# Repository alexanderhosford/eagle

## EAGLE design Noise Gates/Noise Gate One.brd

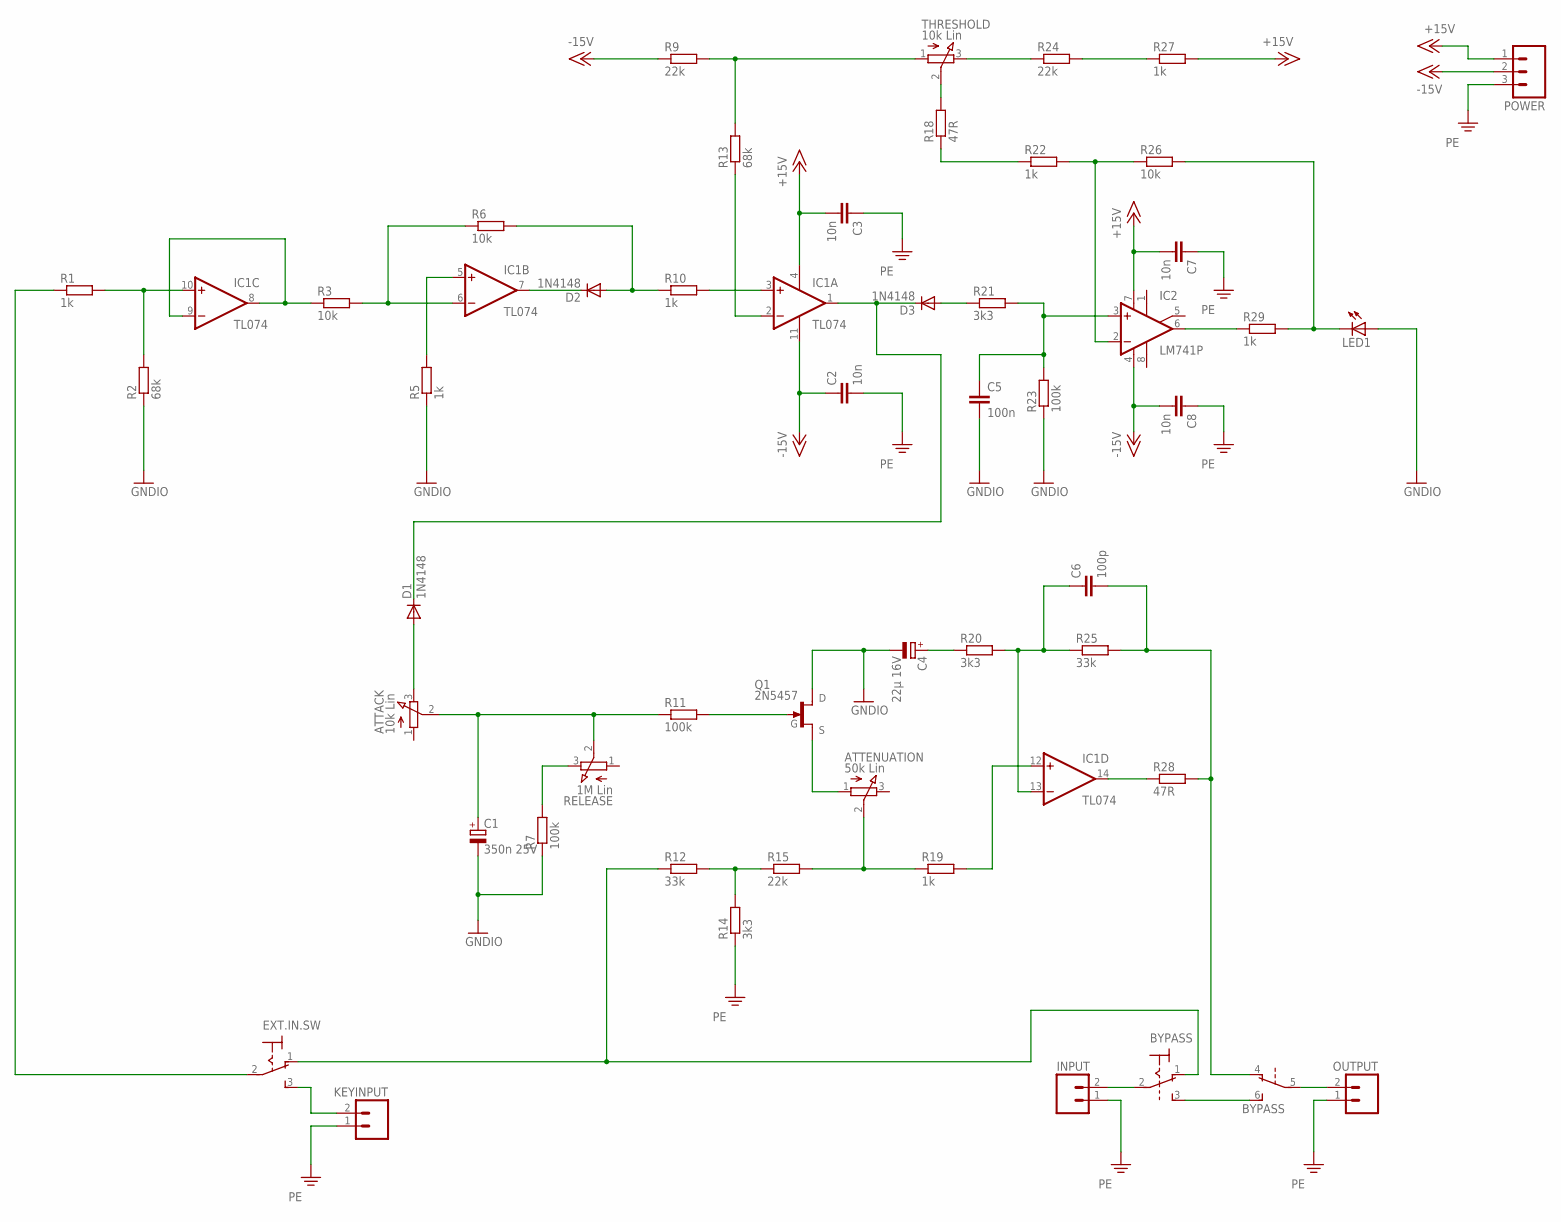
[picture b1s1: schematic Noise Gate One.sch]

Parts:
ATTACK: 10k Lin; 3RP/1610N
ATTENUATION: 50k Lin; 3RP/1610N
BYPASS: M9040P2
C1: 350n 25V; E2,5-7
C2, C3, C7, C8: 10n; C050-035X075
C4: 22µ 16V; E2,5-7
C5: 100n; C050-035X075
C6: 100p; C050-035X075
D1, D2, D3: 1N4148; DO35-7
EXT.IN.SW: M9040P
IC1: TL074; DIL14
IC2: LM741P; DIL08
INPUT: M023.5MM; SCREWTERMINAL-3.5MM-2
KEYINPUT: M023.5MM; SCREWTERMINAL-3.5MM-2
LED1: LED5MM
OUTPUT: M023.5MM; SCREWTERMINAL-3.5MM-2
POWER: M03SCREW; SCREWTERMINAL-3.5MM-3
Q1: 2N5457; TO92-
R1, R5, R10, R19, R22, R27, R29: 1k; 0207/7
R2, R13: 68k; 0207/7
R3, R6, R26: 10k; 0207/7
R7, R11, R23: 100k; 0207/7
R9, R15, R24: 22k; 0207/7
R12, R25: 33k; 0207/7
R14, R20, R21: 3k3; 0207/7
R18, R28: 47R; 0207/7
RELEASE: 1M Lin; 3RP/1610N
THRESHOLD: 10k Lin; 3RP/1610N

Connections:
+15V: C3.2, C7.2, IC1.4 (V+), IC2.7 (V+), POWER.1, R27.2
-15V: C2.1, C8.2, IC1.11 (V-), IC2.4 (V-), POWER.2, R9.1
EXT.IN: EXT.IN.SW.3 (S), KEYINPUT.2
GND: C1.-, C4.-, C5.2, LED1.A, Q1.1 (D), R2.1, R5.1, R7.1, R23.1
unnamed: IC2.6 (OUT), R29.1
unnamed: D2.A, R6.2, R10.1
unnamed: C5.1, IC2.3 (+IN), R21.2, R23.2
unnamed: D3.A, R21.1
unnamed: R9.2, R13.2, THRESHOLD.1 (A)
unnamed: LED1.K (C), R26.2, R29.2
unnamed: D1.C, D3.C, IC1.1 (OUT)
unnamed: IC2.2 (-IN), R22.2, R26.1
unnamed: IC1.3 (+IN), R10.2
unnamed: IC1.2 (-IN), R13.1
unnamed: R24.1, THRESHOLD.3 (E)
unnamed: R24.2, R27.1
unnamed: R18.2, THRESHOLD.2 (S)
unnamed: R18.1, R22.1
unnamed: D2.C, IC1.7 (OUT)
unnamed: IC1.6 (-IN), R3.2, R6.1
unnamed: IC1.5 (+IN), R5.2
unnamed: Q1.3 (G), R11.2
unnamed: IC1.8 (OUT), IC1.9 (-IN), R3.1
unnamed: IC1.10 (+IN), R1.2, R2.2
unnamed: BYPASS.4 (O), C6.2, R25.2, R28.2
unnamed: C4.+, R20.1
unnamed: ATTENUATION.1 (A), Q1.2 (S)
unnamed: ATTENUATION.2 (S), R15.2, R19.1
unnamed: R12.2, R14.2, R15.1
unnamed: IC1.12 (+IN), R19.2
unnamed: C6.1, IC1.13 (-IN), R20.2, R25.1
unnamed: ATTACK.2 (S), C1.+, R11.1, RELEASE.2 (S)
unnamed: IC1.14 (OUT), R28.1
unnamed: R7.2, RELEASE.3 (E)
unnamed: ATTACK.3 (E), D1.A
unnamed: EXT.IN.SW.2, R1.1
unnamed: BYPASS.1 (O), EXT.IN.SW.1 (O), R12.1
unnamed: BYPASS.2, INPUT.2
unnamed: BYPASS.5, OUTPUT.2
unnamed: BYPASS.3 (S), BYPASS.6 (S)
PE: C2.2, C3.1, C7.1, C8.1, INPUT.1, KEYINPUT.1, OUTPUT.1, POWER.3, R14.1

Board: 2 copper layers, 50 parts (0 on the bottom side), 41 nets, no tracks yet.

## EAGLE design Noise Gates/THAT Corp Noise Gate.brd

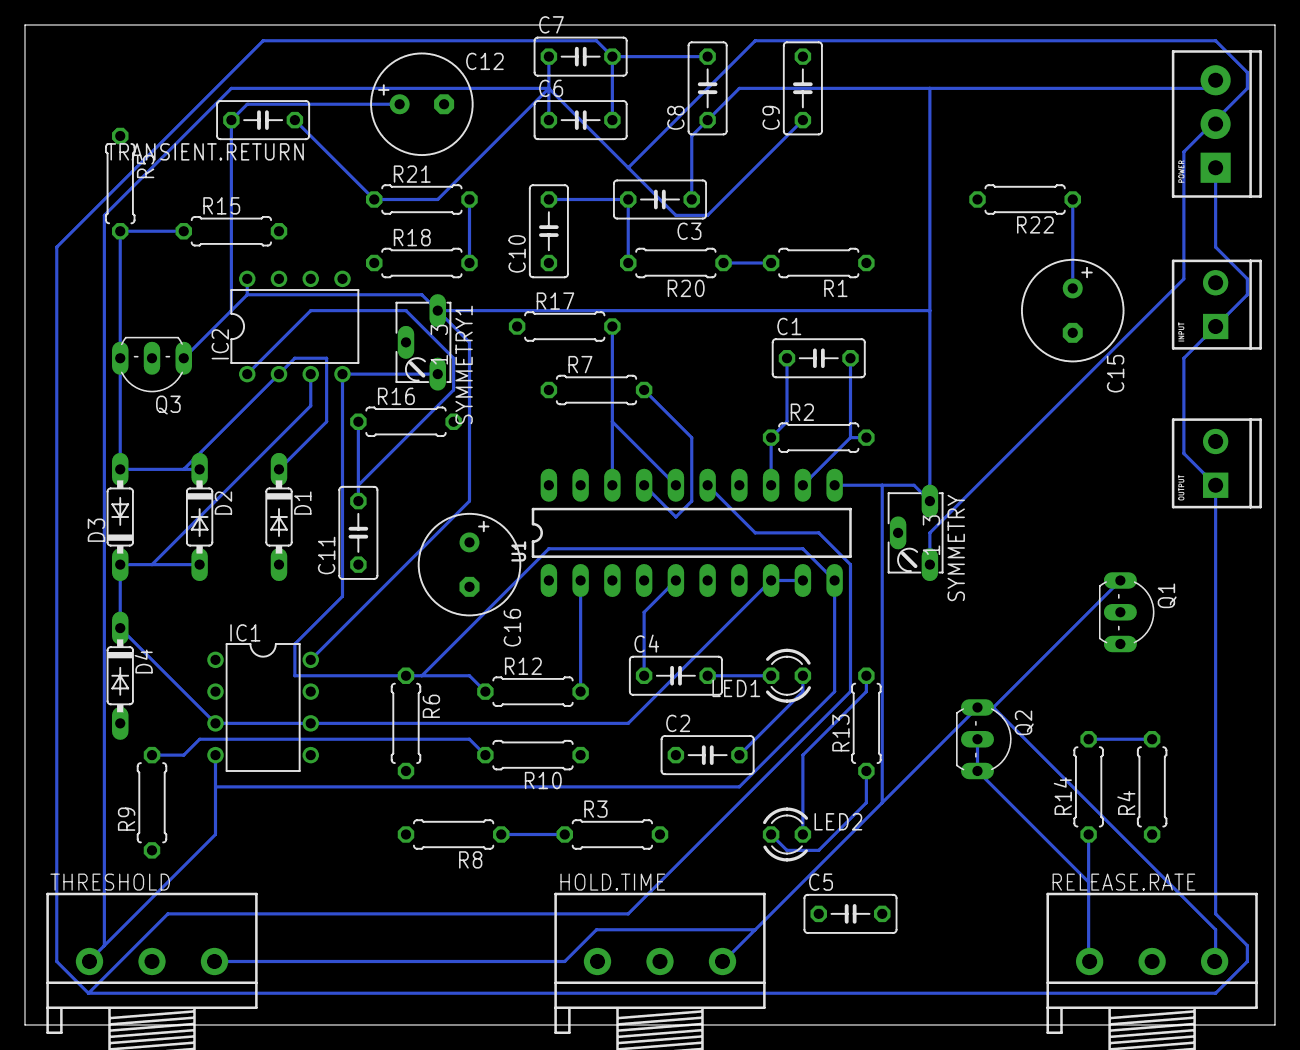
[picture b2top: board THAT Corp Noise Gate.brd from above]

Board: 2 copper layers, 100.0 x 80.0 mm, 55 parts (0 on the bottom side), 34 nets.

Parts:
C1: 47p; C050-030X075
C2, C3, C6, C7, C8, C9, C10: 100n; C050-030X075
C4: 50n; C050-030X075
C5: 2n2; C050-030X075
C11: 220n; C050-030X075
C12: 10µ; E3,5-8
C15, C16: 47µ; E3,5-8
D1, D2, D3, D4: 1N4148; DO35-7
HOLD.TIME: 20k; 3RP/1610N
IC1: LM393N; DIL08
IC2: LF353N; DIL08
INPUT: SCREWTERMINAL-3.5MM-2
LED1, LED2: LED3MM
OUTPUT: SCREWTERMINAL-3.5MM-2
POWER: SCREWTERMINAL-3.5MM-3
Q1, Q2, Q3: 2SA1015; TO92-CBE
R1: 300k; 0207/7
R2, R3, R7: 20k; 0207/7
R4: 30k; 0207/7
R5, R14: 10k; 0207/7
R6, R16: 100k; 0207/7
R8: 5k1; 0207/7
R9: 150k; 0207/7
R10: 2k; 0207/7
R12, R18: 2M; 0207/7
R13: 1M; 0207/7
R15: 1k; 0207/7
R17: 2k49; 0207/7
R20: 51R; 0207/7
R21: 110k; 0207/7
R22: 28k8; 0207/7
RELEASE.RATE: 20k; 3RP/1610N
SYMMETRY, SYMMETRY1: 50k; B64W
THRESHOLD: 50k; 3RP/1610N
TRANSIENT.RETURN: 100n; C050-030X075
U1: THAT4301P20-I; DIL20

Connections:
+15V: C3.1, C8.1, C12.+, HOLD.TIME.3, IC1.8, IC2.8, POWER.3, Q1.E, Q2.E, Q3.E, RELEASE.RATE.3, SYMMETRY.E, SYMMETRY1.E, THRESHOLD.3, TRANSIENT.RETURN.2, U1.11
-15V: C6.1, C7.1, C9.1, IC1.4, IC2.4, POWER.2, R6.1, R12.1, R21.1, SYMMETRY.A, SYMMETRY1.A, THRESHOLD.1, TRANSIENT.RETURN.1, U1.10
GND: D2.A, D3.C, D4.C, IC1.3, IC1.6, IC2.3, U1.8, U1.9
unnamed: R1.2, R20.1, U1.14
unnamed: R1.1, SYMMETRY.S
unnamed: HOLD.TIME.1, Q2.B, Q2.C, R6.2, R8.2, R14.1, RELEASE.RATE.1
unnamed: C1.2, OUTPUT.2, R2.2, U1.12
unnamed: C1.1, R2.1, U1.13
unnamed: HOLD.TIME.2, R3.2
unnamed: R4.1, RELEASE.RATE.2
unnamed: C15.-, R7.1
unnamed: Q3.B, R4.2, R14.2
unnamed: C11.2, IC2.1, R16.1
unnamed: C11.1, D1.A, R15.2
unnamed: R16.2, R17.1
unnamed: C10.1, D4.A, IC1.1, IC1.5, Q1.C
unnamed: IC1.7, R5.1
unnamed: D1.C, D2.C, D3.A, IC2.2, Q3.C, R5.2, R15.1
unnamed: R18.1, SYMMETRY1.S
unnamed: R18.2, R21.2, U1.19
unnamed: R17.2, U1.16, U1.18
unnamed: R9.1, THRESHOLD.2
unnamed: IC1.2, R9.2, R10.2
unnamed: R10.1, U1.4
unnamed: C2.1, C4.1, U1.5
unnamed: C2.2, C5.2, LED1.A, LED2.K, R13.2, U1.7
unnamed: C4.2, C5.1, LED1.K, LED2.A, R13.1, U1.6
unnamed: R12.2, U1.2
unnamed: C16.-, U1.1
unnamed: C16.+, R22.2
unnamed: C15.+, INPUT.2, R22.1
unnamed: Q1.B, R3.1, R8.1
unnamed: R7.2, U1.17
PE: C3.2, C6.2, C7.2, C8.2, C9.2, C10.2, C12.-, INPUT.1, OUTPUT.1, POWER.1, R20.2, U1.15

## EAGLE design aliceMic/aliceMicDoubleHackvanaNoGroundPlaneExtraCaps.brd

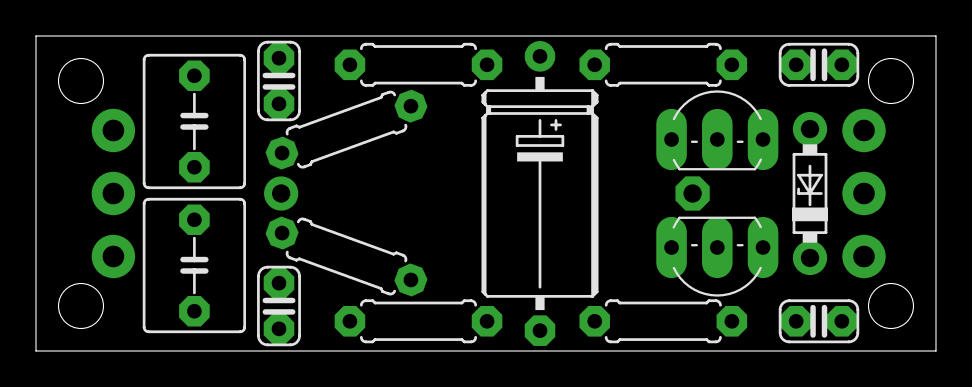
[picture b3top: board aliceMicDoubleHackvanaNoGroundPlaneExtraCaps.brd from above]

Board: 2 copper layers, 50.0 x 17.5 mm, 19 parts (1 on the bottom side), 10 nets, no tracks yet.

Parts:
C1: 100µ; E22-9
C2, C3: µ47; C050-055X075
C4: 10µ; E15-6
C5, C6: 22n; C025-024X044
C7, C8: 470p; C025-024X044
D1: 12V; 7MMGRIDZENER
FET_D_S_1G: 3.5MM_PADS
R1, R2: 2k2; 0207/7
R3: 330R; 0207/7
R4, R5: 100k; 0207/7
R6: 6k8; 0207/7
T1, T2: 2N5087; TO92-EBC
XLR: 3.5MM_PADS

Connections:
GND: C1.-, C4.-, C5.2, C6.1, D1.A, FET_D_S_1G.1, R2.1, XLR.2
unnamed: C4.+, D1.C, R3.2, R6.2
unnamed: C7.2, C8.1, R4.1, R5.2, R6.1, T1.C, T2.C
unnamed: C5.1, T1.E, XLR.3
unnamed: C6.2, T2.E, XLR.1
unnamed: C2.2, C7.1, R4.2, T1.B
unnamed: C3.1, C8.2, R5.1, T2.B
unnamed: C1.+, R1.2, R3.1
unnamed: C2.1, FET_D_S_1G.3, R1.1
unnamed: C3.2, FET_D_S_1G.2, R2.2

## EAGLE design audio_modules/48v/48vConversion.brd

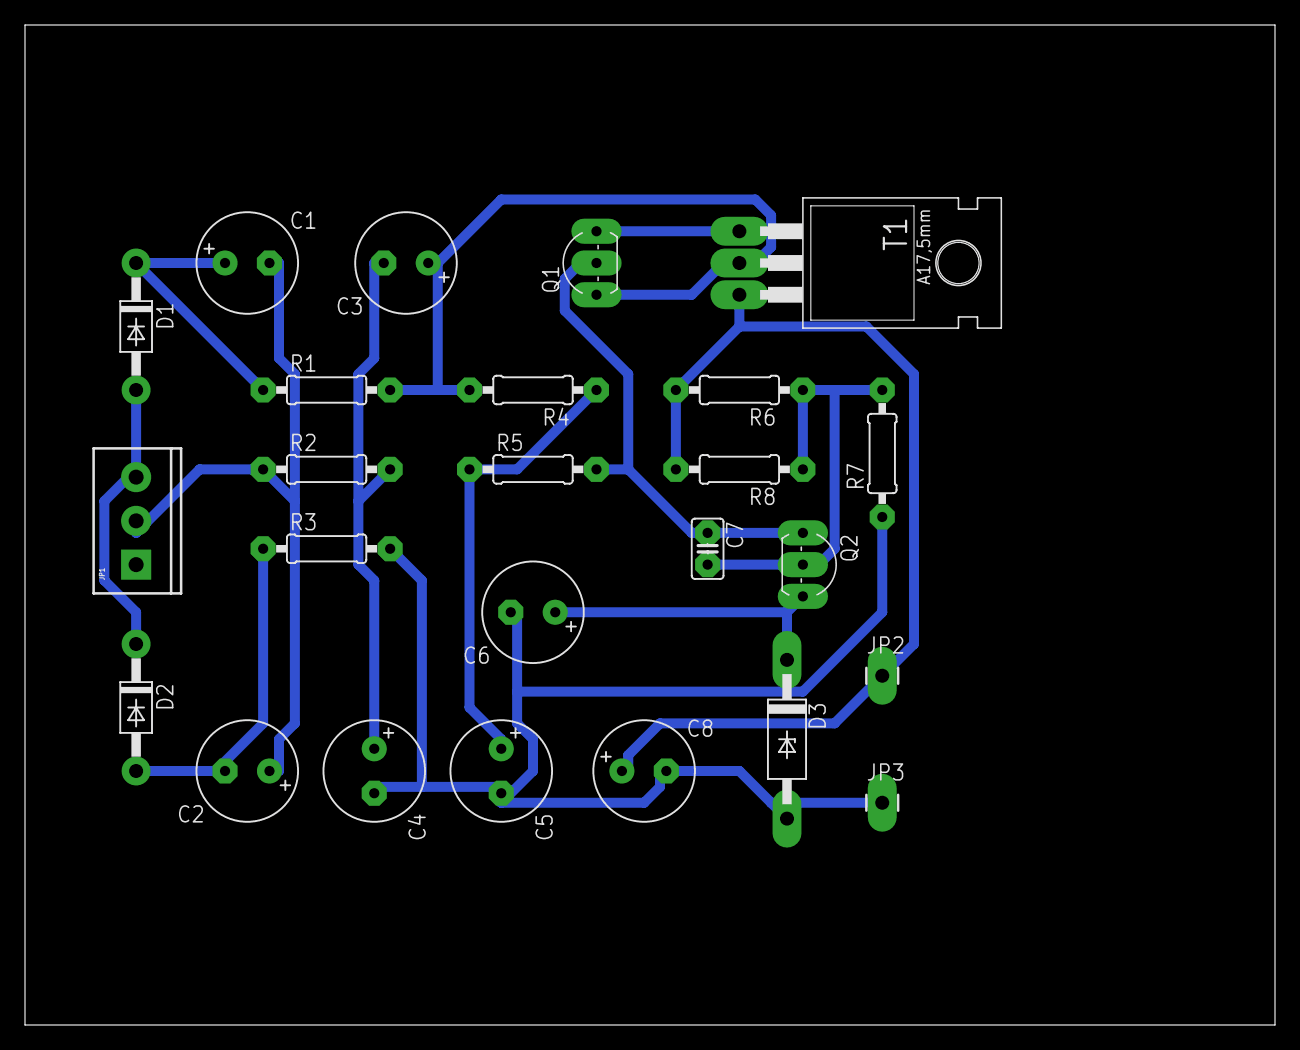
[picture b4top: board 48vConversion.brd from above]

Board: 2 copper layers, 100.0 x 80.0 mm, 25 parts (0 on the bottom side), 13 nets.

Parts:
C1, C2, C3, C4: 1000µF 50V; E3,5-8
C5: 100µF 63V; E3,5-8
C6: 10µF 50V; E3,5-8
C7: 220pF 50V; C025-025X050
C8: 100µF 50V; E3,5-8
D1, D2: 1N4004; DO41-10
D3: 24V; P1Z12
JP1: AC; SCREWTERMINAL-3.5MM-3
JP2: 48V; 1X01_LONGPAD
JP3: GND; 1X01_LONGPAD
Q1, Q2: BC546B; TO92-EBC
R1, R3: 22R/1W; 0207/10
R2: 100k; 0207/10
R4, R5, R6, R7, R8: 10k; 0207/10
T1: BD139; TO220

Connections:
GND: C4.-, C5.-, C6.-, C8.-, D3.A, JP3.1, R3.2, R7.1
unnamed: C1.-, C2.+, JP1.2, R2.1
unnamed: C1.+, D1.C, R1.1
unnamed: C6.+, D3.C, Q2.E
unnamed: C3.+, Q1.C, R1.2, R4.2, T1.2
unnamed: C3.-, C4.+, R2.2
unnamed: C5.+, R4.1, R5.1
unnamed: D1.A, D2.C, JP1.3
unnamed: C7.2, Q2.B, R6.1, R7.2, R8.1
unnamed: C7.1, Q1.B, Q2.C, R5.2
unnamed: C2.-, D2.A, R3.1
unnamed: Q1.E, T1.1
unnamed: C8.+, JP2.1, R6.2, R8.2, T1.3

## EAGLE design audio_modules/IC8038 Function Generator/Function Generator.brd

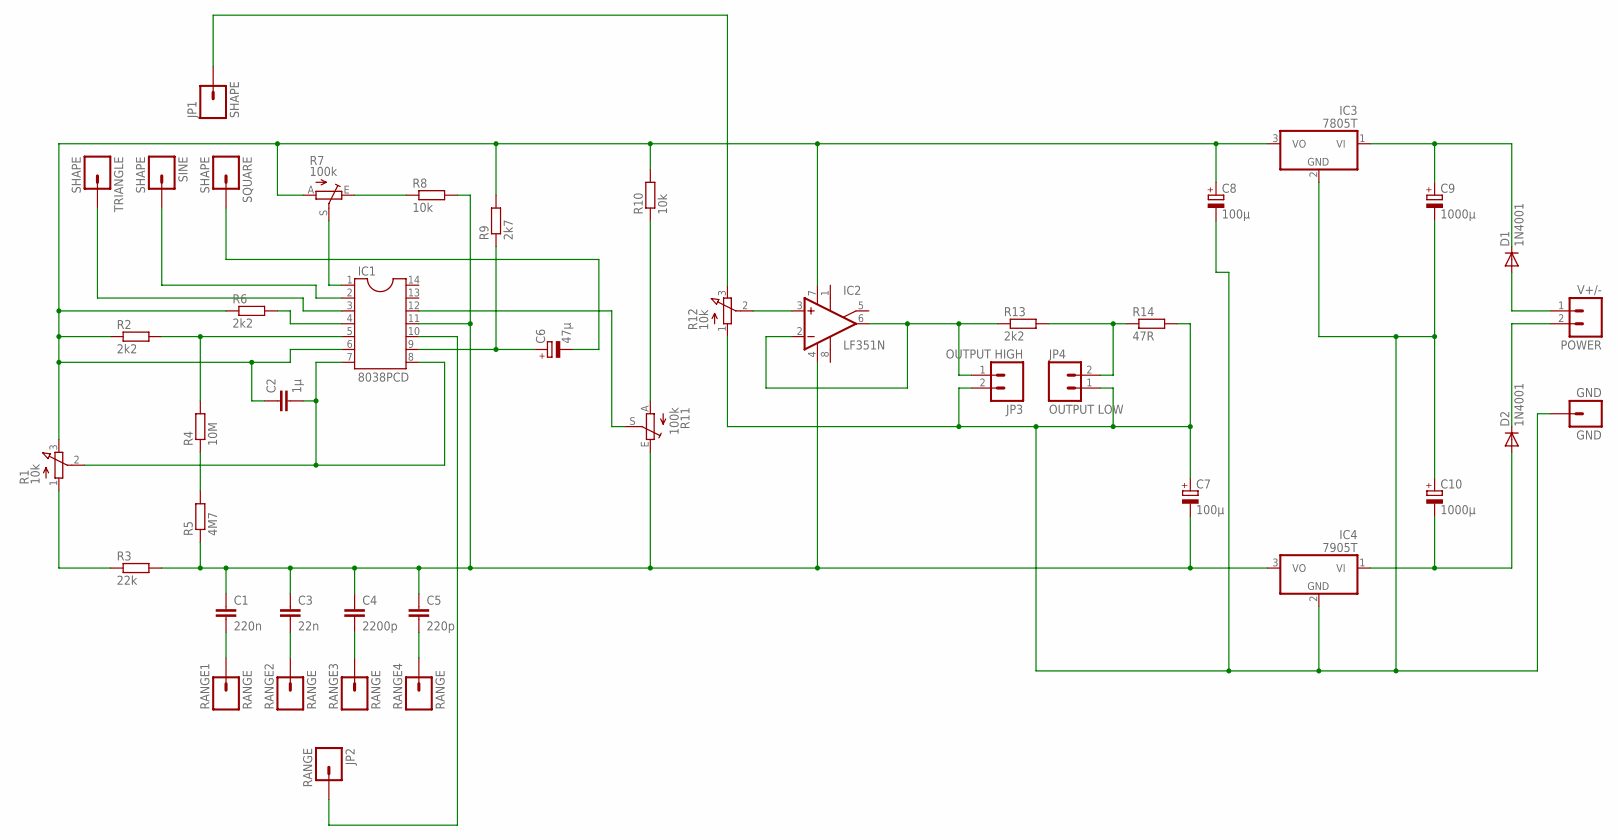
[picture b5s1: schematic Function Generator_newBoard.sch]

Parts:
C1: 220n; C050-035X075
C2: 1µ; C050-035X075
C3: 22n; C050-035X075
C4: 2200p; C050-035X075
C5: 220p; C050-035X075
C6: 47µ; E5-10,5
C7, C8: 100µ; E3,5-8
C9, C10: 1000µ; E5-10,5
D1, D2: 1N4001; DO41-10
GND: GND; 1X01_LONGPAD
IC1: 8038PCD; DIL14
IC2: LF351N; DIL08
IC3: 7805T; TO220H
IC4: 7905T; TO220H
JP1: SHAPE; 1X01_LONGPAD
JP2: RANGE; 1X01_LONGPAD
JP3: OUTPUT HIGH; SCREWTERMINAL-3.5MM-2
JP4: OUTPUT LOW; SCREWTERMINAL-3.5MM-2
POWER: V+/-; SCREWTERMINAL-3.5MM-2
R1, R12: 10k; 3RP/1610N
R2, R6, R13: 2k2; 0207/10
R3: 22k; 0207/10
R4: 10M; 0207/10
R5: 4M7; 0207/10
R7, R11: 100k; S64Y
R8, R10: 10k; 0207/10
R9: 2k7; 0207/10
R14: 47R; 0207/10
RANGE1, RANGE2, RANGE3, RANGE4: RANGE; 1X01_LONGPAD
SINE: SHAPE; 1X01_LONGPAD
SQUARE: SHAPE; 1X01_LONGPAD
TRIANGLE: SHAPE; 1X01_LONGPAD

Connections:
GND: C7.+, C8.-, C9.-, C10.+, GND.1, IC3.2 (GND), IC4.2 (GND), JP3.2, JP4.1, R12.1 (A), R14.2
unnamed: IC1.4 (DUTYCYCLE), R6.2
unnamed: IC1.5 (FREQUENCYADJUST), R2.2, R4.2
unnamed: C2.1, C8.+, IC1.6 (V+), IC2.7 (V+), IC3.3 (VO), R1.3 (E), R2.1, R6.1, R7.A, R9.2, R10.2
unnamed: C2.2, IC1.7 (FMBIAS), IC1.8 (FMSWEEPINPUT), R1.2 (S)
unnamed: R4.1, R5.2
unnamed: C1.1, C3.1, C4.1, C5.1, C7.-, IC1.11 (V-ORGROUND), IC2.4 (V-), IC4.3 (VO), R3.2, R5.1, R8.2, R11.E
unnamed: R1.1 (A), R3.1
unnamed: C3.2, RANGE2.1
unnamed: C4.2, RANGE3.1
unnamed: C1.2, RANGE1.1
unnamed: C5.2, RANGE4.1
unnamed: IC1.10 (TIMINGCAPACITOR), JP2.1
unnamed: C6.+, IC1.9 (SQUAREWAVEOUT), R9.1
unnamed: R7.E, R8.1
unnamed: IC2.2 (-IN), IC2.6 (OUT), JP3.1, R13.1
unnamed: IC1.3 (TRIANGLEOUT), TRIANGLE.1
unnamed: IC1.2 (SINEWAVEOUT), SINE.1
unnamed: IC1.1 (SINEWAVEADJUST), R7.S
unnamed: C6.-, SQUARE.1
unnamed: R10.1, R11.A
unnamed: IC1.12 (SINEWAVEADJUST2), R11.S
unnamed: IC2.3 (+IN), R12.2 (S)
unnamed: JP1.1, R12.3 (E)
unnamed: JP4.2, R13.2, R14.1
unnamed: C10.-, D2.A, IC4.1 (VI)
unnamed: C9.+, D1.C, IC3.1 (VI)
unnamed: D1.A, POWER.1
unnamed: D2.C, POWER.2

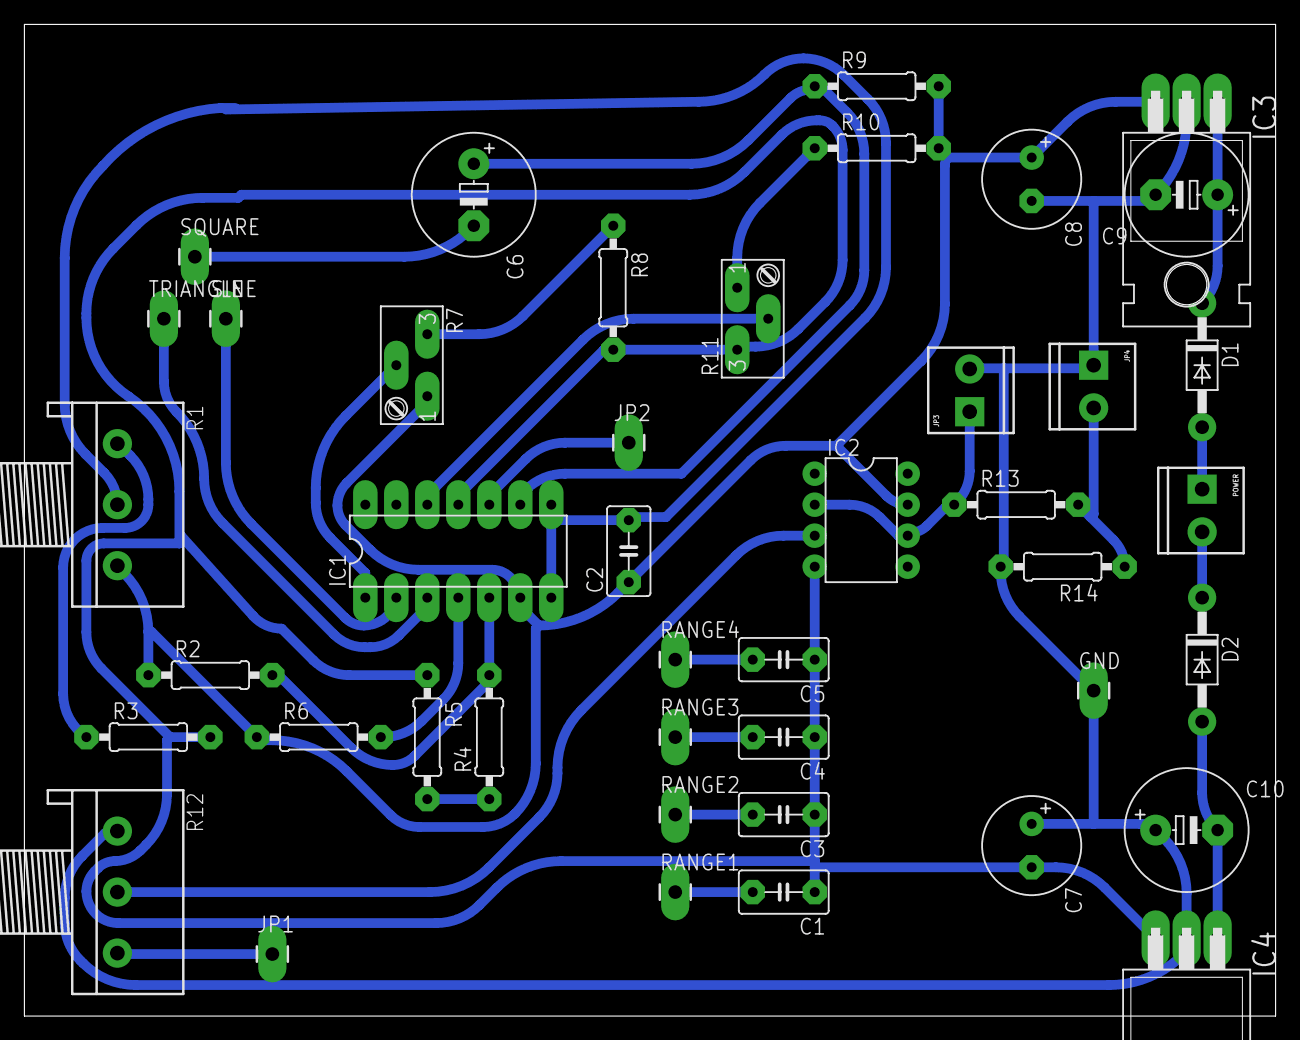
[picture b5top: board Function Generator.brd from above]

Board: 2 copper layers, 102.5 x 81.3 mm, 43 parts (0 on the bottom side), 29 nets.

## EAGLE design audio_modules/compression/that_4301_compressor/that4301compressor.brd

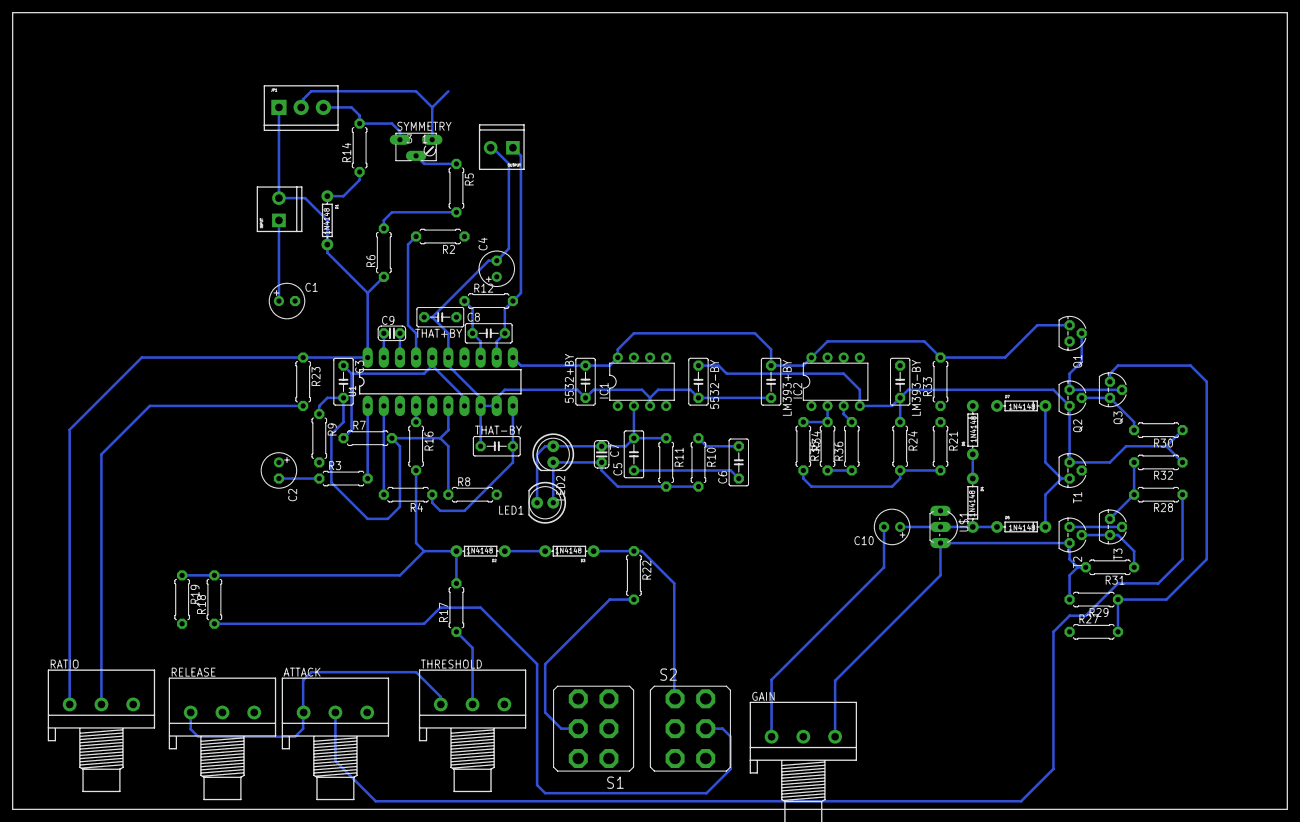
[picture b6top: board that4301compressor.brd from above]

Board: 2 copper layers, 200.6 x 125.4 mm, 76 parts (0 on the bottom side), 46 nets.

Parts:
5532+BY, 5532-BY: 100n; C050-030X075
ATTACK: 10k; 3RP/1610N
C1, C2: 47µ; E2,5-6
C3: 100n MY; C050-030X075
C4: 22µ; E2,5-6
C5: 50n; C050-030X075
C6: 470n; C050-030X075
C7: 2n; C025-024X044
C8: 47p NPO 5%; C050-030X075
C9: 22p; C025-024X044
C10: 4µ7; E2,5-6
D1, D2, D3, D4, D5, D6, D7: 1N4148; DIODE-1N4148
GAIN: 3RP/1610N
IC1: NE5532N; DIL08
IC2: LM393N; DIL08
INPUT: SCREWTERMINAL-3.5MM-2
JP1: POWER; SCREWTERMINAL-3.5MM-3
LED1, LED2: LED5MM
LM393+BY, LM393-BY: 100n; C050-030X075
OUTPUT: SCREWTERMINAL-3.5MM-2
Q1, Q2, Q3: 2N3906; TO92
R2, R12: 20k; 0207/7
R3: 28k8; 0207/7
R4, R11: 2M; 0207/7
R5: 300k 5%; 0207/7
R6: 51R 5%; 0207/7
R7, R16: 5k1 3300ppm; 0207/7
R8, R18, R19, R21: 30k1; 0207/7
R9, R17: 590k; 0207/7
R10: 150R; 0207/7
R14: 220k; 0207/7
R22: 1k4; 0207/7
R23: 15k; 0207/7
R24, R33: 5k1; 0207/7
R27: 127k; 0207/7
R28: 12k7; 0207/7
R29: 510R; 0207/7
R30: 18M; 0207/7
R31: 1M8; 0207/7
R32: 51R; 0207/7
R34, R35: 10k; 0207/7
R36: 30k; 0207/7
RATIO: 10k; 3RP/1610N
RELEASE: 50k; 3RP/1610N
S1: VAR ATTACK/RELEASE; M9040P2
S2: HARD/SOFT KNEE; M9040P2
SYMMETRY: 50k; B64W
T1, T2, T3: 2N3904; TO92
THAT+BY: 100n; C050-030X075
THAT-BY: 100n; C050-030X075
THRESHOLD: 50k; 3RP/1610N
U1: THAT4301P20-I; DIL20
U$1: 2SK170"; TO92-

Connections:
GND: 5532+BY.1, 5532-BY.2, C4.-, D1.C, IC1.3, INPUT.2, JP1.1, LM393+BY.2, LM393-BY.1, OUTPUT.2, R6.1, R23.1, R35.1, R36.1, RATIO.1, THAT+BY.2, THAT-BY.1, U1.8, U1.9, U1.15, U1.20
unnamed: R2.2, U1.17
unnamed: C1.-, R2.1
unnamed: R5.1, SYMMETRY.S
unnamed: R5.2, R6.2, U1.14
unnamed: 5532-BY.1, ATTACK.1, C10.-, GAIN.1, IC1.4, IC2.4, JP1.2, LM393-BY.2, Q2.1, R4.1, R24.1, R30.1, R32.1, RELEASE.1, SYMMETRY.A, T1.3, THAT-BY.2, THRESHOLD.1, U1.10
unnamed: C8.1, R12.1, U1.13
unnamed: C8.2, OUTPUT.1, R12.2, U1.12
unnamed: C3.1, R7.1, U1.7, U1.16
unnamed: C1.+, C2.+, INPUT.1
unnamed: C3.2, R7.2, R8.1, R9.1, U1.6
unnamed: GAIN.2, R9.2
unnamed: R8.2, S1.2
unnamed: C6.2, R10.1
unnamed: C5.1, C6.1, U1.5
unnamed: C5.2, C7.1, IC1.2, LED1.K, LED2.A, R11.1
unnamed: C7.2, IC1.1, LED1.A, LED2.K, R10.2, R11.2
unnamed: R4.2, U1.2
unnamed: R3.2, U1.1
unnamed: R19.2, S2.2
unnamed: C2.-, R3.1
unnamed: R16.1, U1.4
unnamed: C9.1, D2.C, R16.2, R17.2, R18.2, R19.1, U1.19
unnamed: C9.2, D2.A, D3.C, U1.18
unnamed: R17.1, THRESHOLD.2
unnamed: R18.1, S2.5
unnamed: D1.A, R14.1, S2.6
unnamed: R21.1, S1.1
unnamed: D3.A, R22.1, RATIO.3, S2.1
unnamed: R22.2, R23.2, RATIO.2, S1.5
unnamed: R27.1, RELEASE.2
unnamed: R21.2, R24.2, R34.2, U$1.3
unnamed: C10.+, D4.C, D5.A, U$1.2
unnamed: D5.C, D7.C, T1.1
unnamed: Q3.3, R27.2, R29.1
unnamed: D4.A, D6.A, Q1.1
unnamed: D6.C, D7.A, IC2.1, R33.1
unnamed: T1.2, T2.3, T3.2
unnamed: R28.2, R32.2, T3.3
unnamed: ATTACK.2, R28.1
unnamed: R31.1, T2.2, T3.1
unnamed: 5532+BY.2, ATTACK.3, C4.+, GAIN.3, IC1.8, IC2.8, JP1.3, LM393+BY.1, Q1.3, R14.2, R29.2, R31.2, R33.2, RELEASE.3, SYMMETRY.E, T2.1, THAT+BY.1, THRESHOLD.3, U1.11, U$1.1
unnamed: Q1.2, Q2.3, Q3.2
unnamed: Q2.2, Q3.1, R30.2
unnamed: IC2.2, R34.1, R35.2
unnamed: IC2.3, R36.2, S1.4

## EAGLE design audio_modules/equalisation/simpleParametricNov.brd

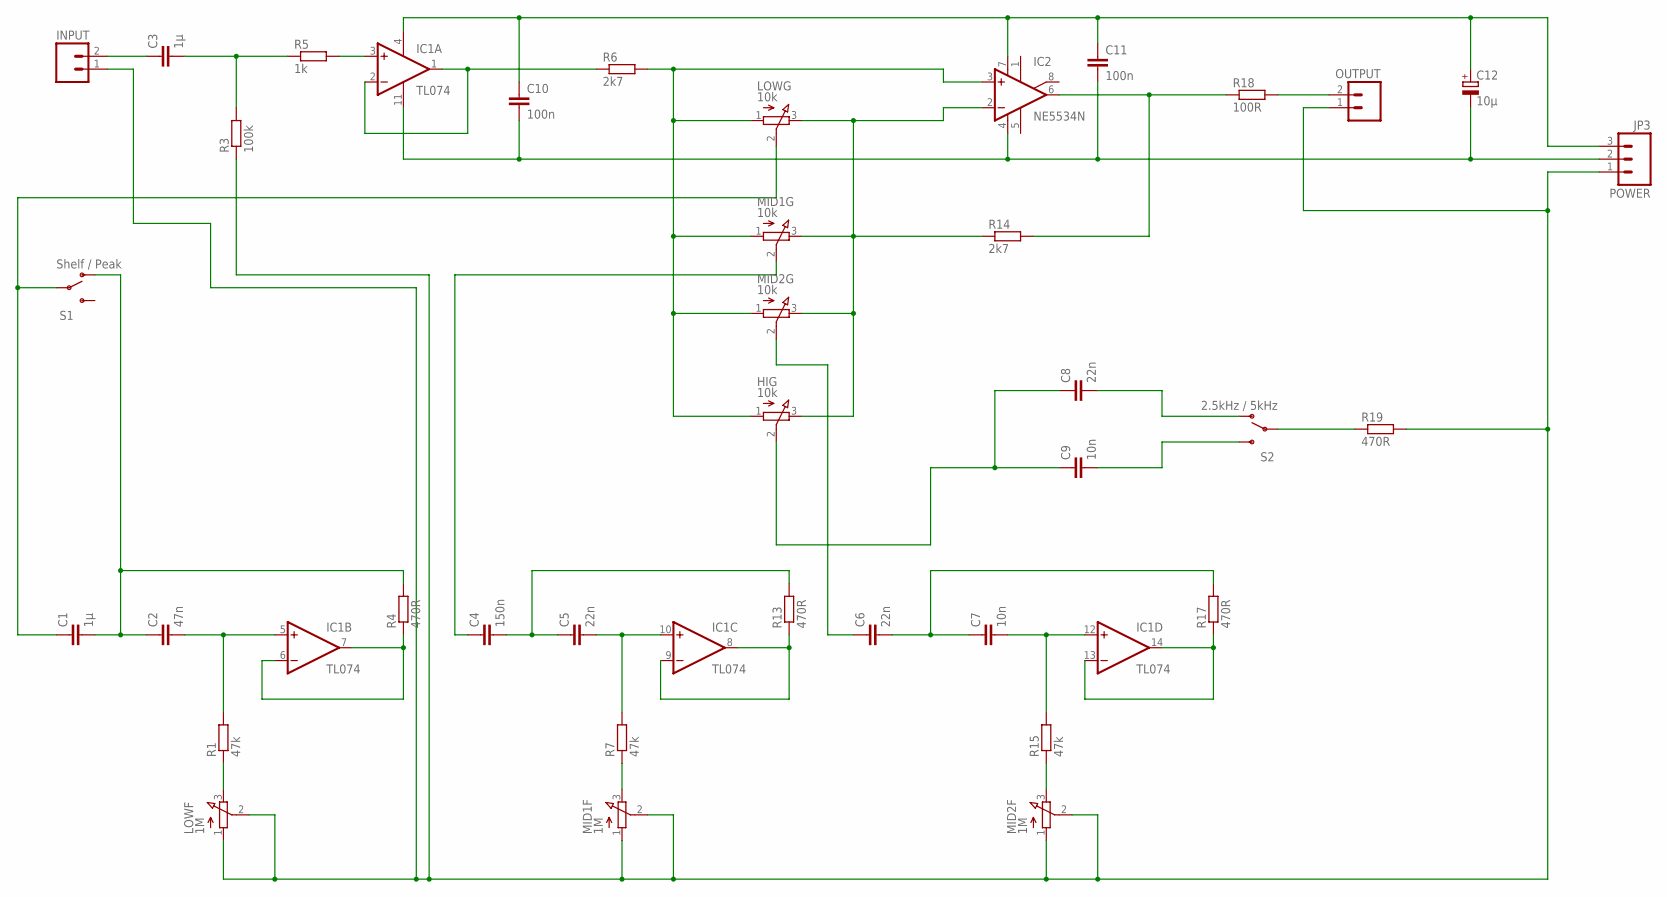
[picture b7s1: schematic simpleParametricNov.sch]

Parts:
C1, C3: 1µ; C050-025X075
C2: 47n; C050-025X075
C4: 150n; C050-025X075
C5, C6, C8: 22n; C025-024X044
C7, C9: 10n; C025-024X044
C10, C11: 100n; C050-025X075
C12: 10µ; E2,5-6E
HIG: 10k; 3RP/1610N
IC1: TL074; DIL14
IC2: NE5534N; DIL08
INPUT: M02PTH; 1X02
JP3: POWER; SCREWTERMINAL-3.5MM-3
LOWF: 1M; 3RP/1610N
LOWG: 10k; 3RP/1610N
MID1F, MID2F: 1M; 3RP/1610N
MID1G, MID2G: 10k; 3RP/1610N
OUTPUT: M02PTH; 1X02
R1, R7, R15: 47k; 0207/7
R3: 100k; 0207/7
R4, R13, R17, R19: 470R; 0207/7
R5: 1k; 0207/7
R6, R14: 2k7; 0207/7
R18: 100R; 0207/7
S1: Shelf / Peak; SWITCH-SPDT
S2: 2.5kHz / 5kHz; SWITCH-SPDT

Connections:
GND: INPUT.1, JP3.1, LOWF.1 (A), LOWF.2 (S), MID1F.1 (A), MID1F.2 (S), MID2F.1 (A), MID2F.2 (S), OUTPUT.1, R3.1, R19.2
unnamed: C1.2, C2.1, R4.2, S1.1 (O)
unnamed: C4.2, C5.1, R13.2
unnamed: C6.2, C7.1, R17.2
unnamed: C9.2, S2.3 (S)
unnamed: C8.2, S2.1 (O)
unnamed: R19.1, S2.2
unnamed: IC1.13 (-IN), IC1.14 (OUT), R17.1
unnamed: C7.2, IC1.12 (+IN), R15.2
unnamed: MID2F.3 (E), R15.1
unnamed 10: C3.1, INPUT.2; also elsewhere on the board
unnamed: C3.2, R3.2, R5.1
unnamed: IC1.3 (+IN), R5.2
unnamed: IC1.1 (OUT), IC1.2 (-IN), R6.1
unnamed: HIG.1 (A), IC2.3 (+IN), LOWG.1 (A), MID1G.1 (A), MID2G.1 (A), R6.2
unnamed: IC2.6 (OUT), R14.2, R18.1
unnamed 16: OUTPUT.2, R18.2; also elsewhere on the board
unnamed: HIG.3 (E), IC2.2 (-IN), LOWG.3 (E), MID1G.3 (E), MID2G.3 (E), R14.1
unnamed: IC1.6 (-IN), IC1.7 (OUT), R4.1
unnamed: C2.2, IC1.5 (+IN), R1.2
unnamed: LOWF.3 (E), R1.1
unnamed: C1.1, LOWG.2 (S), S1.2
unnamed: IC1.8 (OUT), IC1.9 (-IN), R13.1
unnamed: C5.2, IC1.10 (+IN), R7.2
unnamed: MID1F.3 (E), R7.1
unnamed: C6.1, MID2G.2 (S)
unnamed: C8.1, C9.1, HIG.2 (S)
V+: C10.1, C11.1, C12.+, IC1.4 (V+), IC2.7 (V+), JP3.3
V-: C10.2, C11.2, C12.-, IC1.11 (V-), IC2.4 (V-), JP3.2
VIA1: C4.1, MID1G.2 (S)

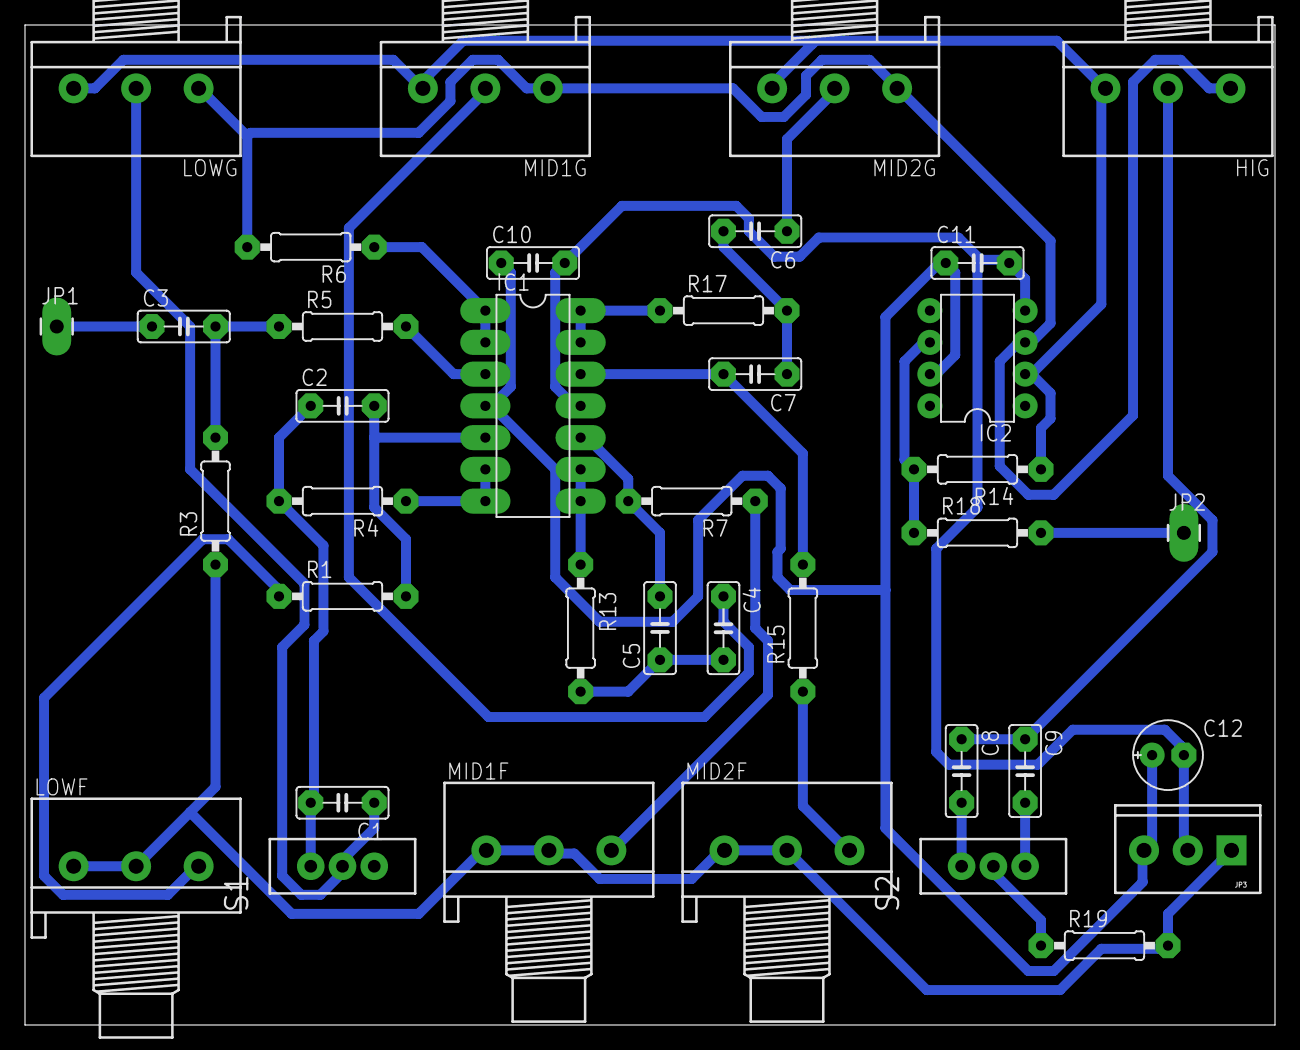
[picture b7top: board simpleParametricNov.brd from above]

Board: 2 copper layers, 100.0 x 80.0 mm, 38 parts (0 on the bottom side), 30 nets.

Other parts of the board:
JP1: INPUT; 1X01_LONGPAD
JP2: OUTPUT; 1X01_LONGPAD

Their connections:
unnamed 10: JP1.1; also elsewhere on the board
unnamed 16: JP2.1; also elsewhere on the board

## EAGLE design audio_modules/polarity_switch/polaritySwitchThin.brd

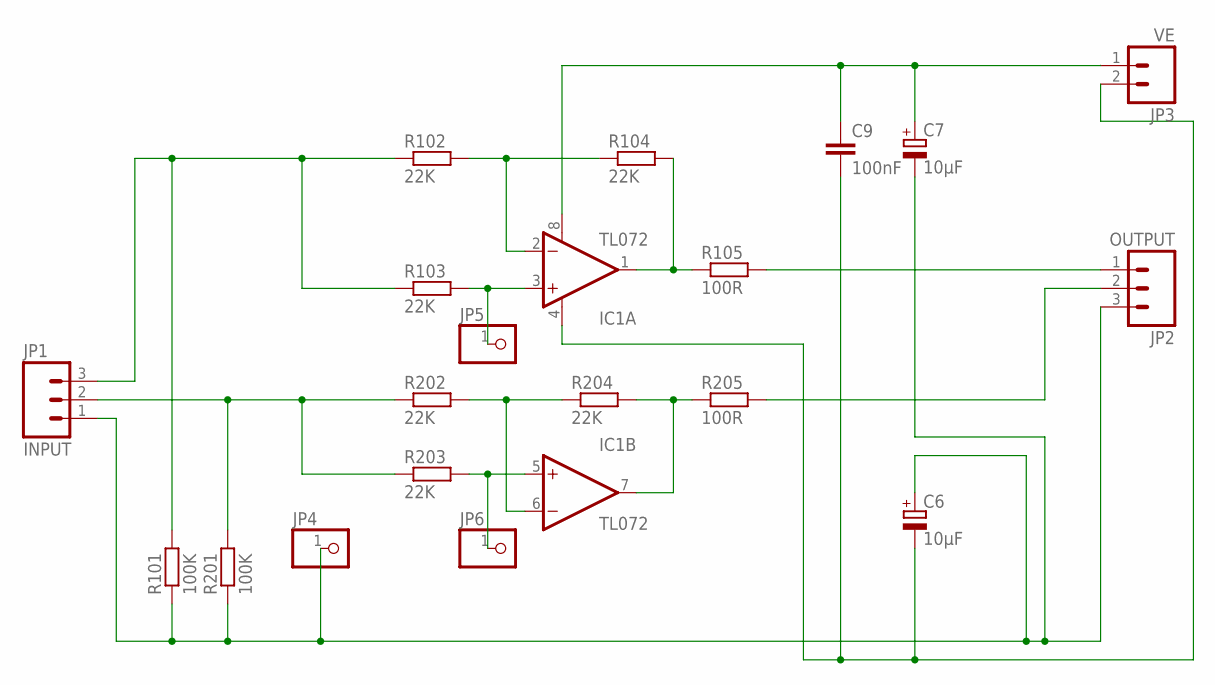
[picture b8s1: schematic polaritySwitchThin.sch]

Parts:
C6, C7: 10µF; E2,5-6
C9: 100nF; C050-030X075
IC1: TL072; DIP08
JP1: INPUT; SCREWTERMINAL-3.5MM-3
JP2: OUTPUT; SCREWTERMINAL-3.5MM-3
JP3: VE; SCREWTERMINAL-3.5MM-2
JP4, JP5, JP6: PINHD-1X1; 1X01
R101, R201: 100K; 0207/10
R102, R103, R104, R202, R203, R204: 22K; 0207/10
R105, R205: 100R; 0207/10

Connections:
unnamed: C7.+, C9.1, IC1.8 (V+), JP3.1
unnamed: IC1.1 (OUT), R104.2, R105.1
unnamed: IC1.5 (+IN), JP6.1, R203.2
unnamed: JP1.2, R201.2, R202.1, R203.1
unnamed: IC1.3 (+IN), JP5.1, R103.2
unnamed: IC1.7 (OUT), R204.2, R205.1
unnamed: IC1.6 (-IN), R202.2, R204.1
unnamed: C6.-, C9.2, IC1.4 (V-), JP3.2
unnamed: C6.+, C7.-, JP1.1, JP2.3, JP4.1, R101.1, R201.1
unnamed: JP1.3, R101.2, R102.1, R103.1
unnamed: IC1.2 (-IN), R102.2, R104.1
unnamed: JP2.2, R205.2
unnamed: JP2.1, R105.2

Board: 2 copper layers, 20 parts (0 on the bottom side), 13 nets, no tracks yet.

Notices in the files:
parts and their libraries:
SparkFun: Licensing: CC v3.0 Share-Alike You are welcome to use this library for commercial purposes.
